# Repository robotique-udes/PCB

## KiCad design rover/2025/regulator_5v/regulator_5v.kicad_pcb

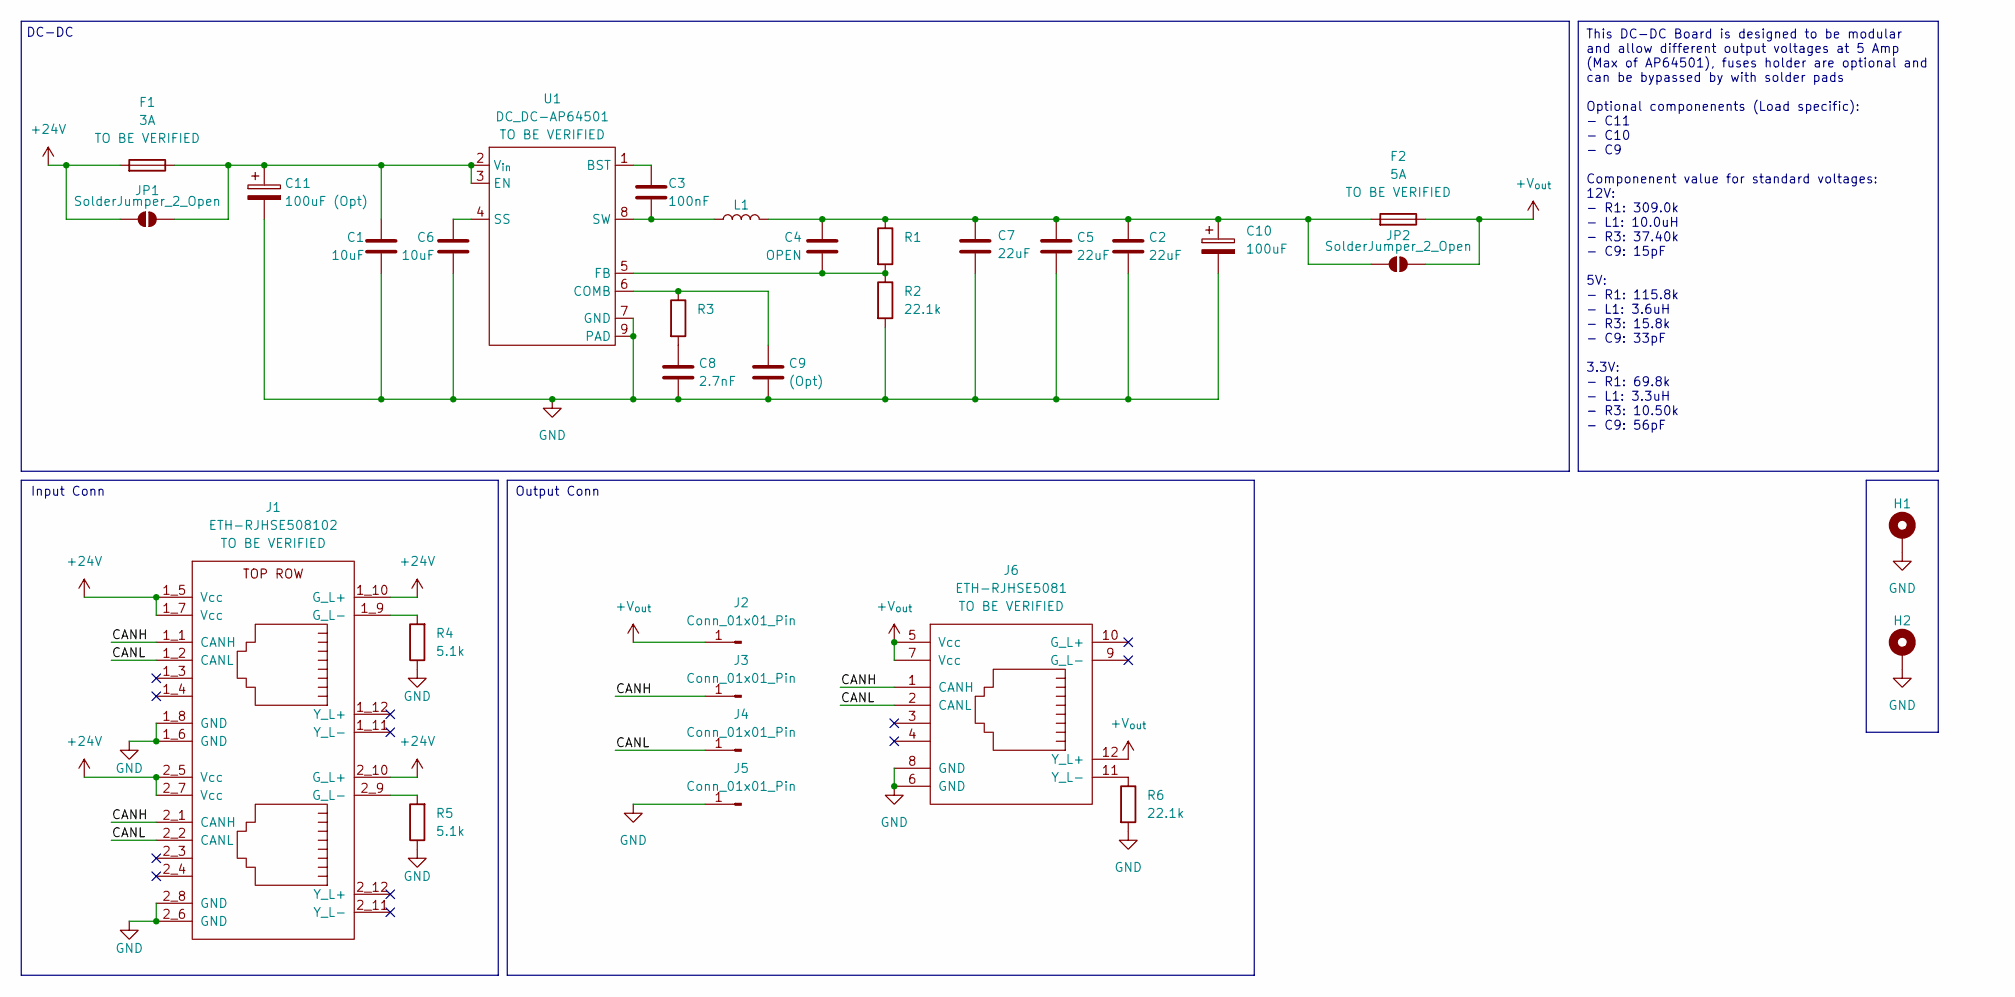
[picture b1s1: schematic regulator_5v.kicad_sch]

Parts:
C1, C6: 10uF; C_0805_2012Metric_Pad1.18x1.45mm_HandSolder
C2, C5, C7: 22uF; C_0805_2012Metric_Pad1.18x1.45mm_HandSolder
C3: 100nF; C_0805_2012Metric_Pad1.18x1.45mm_HandSolder
C4: OPEN; C_0805_2012Metric_Pad1.18x1.45mm_HandSolder
C8: 2.7nF; C_0805_2012Metric_Pad1.18x1.45mm_HandSolder
C9: (Opt); C_0805_2012Metric_Pad1.18x1.45mm_HandSolder
C10: 100uF; CP_Elec_6.3x7.7
C11: 100uF (Opt); CP_Elec_6.3x7.7
F1: 3A; FuseHolder-3588-20
F2: 5A; FuseHolder-3588-20
H1, H2: MountingHole_Pad; MountingHole_3.2mm_M3_DIN965_Pad_TopBottom
J1: ETH-RJHSE508102
J2, J3, J4, J5: Conn_01x01_Pin; Pad_SMD_1x3mm
J6: ETH-RJHSE5081
JP1, JP2: SolderJumper_2_Open; SolderJumper-2_P1.3mm_Open_TrianglePad1.0x1.5mm
L1: L_SXN_SMDRI125
R1, R3: C_0805_2012Metric_Pad1.18x1.45mm_HandSolder
R2, R6: 22.1k; C_0805_2012Metric_Pad1.18x1.45mm_HandSolder
R4, R5: 5.1k; R_0805_2012Metric_Pad1.20x1.40mm_HandSolder
U1: DC_DC-AP64501; SOIC-8-1EP_3.9x4.9mm_P1.27mm_EP2.29x3mm

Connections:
+24V: F1.1, J1.1_5 (Vcc), J1.1_7 (Vcc), J1.1_10 (G_L+), J1.2_5 (Vcc), J1.2_7 (Vcc), J1.2_10 (G_L+), JP1.1 (A)
+V_{out}: F2.2, J2.1, J6.5 (Vcc), J6.7 (Vcc), J6.12 (Y_L+), JP2.2 (B)
/CANH: J1.1_1 (CANH), J1.2_1 (CANH), J3.1, J6.1 (CANH)
/CANL: J1.1_2 (CANL), J1.2_2 (CANL), J4.1, J6.2 (CANL)
GND: C1.1, C2.1, C5.1, C6.1, C7.1, C8.1, C9.1, C10.2, C11.2, H1.1, H2.1, J1.1_6 (GND), J1.1_8 (GND), J1.2_6 (GND), J1.2_8 (GND), J5.1, J6.6 (GND), J6.8 (GND), R2.2, R4.1, R5.1, R6.2, U1.7 (GND), U1.9 (PAD)
unnamed: C8.2, R3.2
unnamed: J1.1_9 (G_L-), R4.2
unnamed: J1.2_9 (G_L-), R5.2
unnamed: J6.11 (Y_L-), R6.1
unnamed: C1.2, C11.1, F1.2, JP1.2 (B), U1.2 (V_{in}), U1.3 (EN)
unnamed: C2.2, C4.2, C5.2, C7.2, C10.1, F2.1, JP2.1 (A), L1.2, R1.1
unnamed: C3.1, L1.1, U1.8 (SW)
unnamed: C9.2, R3.1, U1.6 (COMB)
unnamed: C6.2, U1.4 (SS)
unnamed: C3.2, U1.1 (BST)
unnamed: C4.1, R1.2, R2.1, U1.5 (FB)

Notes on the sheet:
This DC-DC Board is designed to be modular and allow different output voltages at 5 Amp (Max of AP64501), fuses holder are optional and can be bypassed by with solder pads Optional componenents (Load specific): - C11 - C10 - C9 Componenent value for standard voltages: 12V: - R1: 309.0k - L1: 10.0uH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
Input Conn
DC-DC
Output Conn

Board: 2 copper layers, 31 parts (17 on the bottom side), 16 nets, no tracks yet.

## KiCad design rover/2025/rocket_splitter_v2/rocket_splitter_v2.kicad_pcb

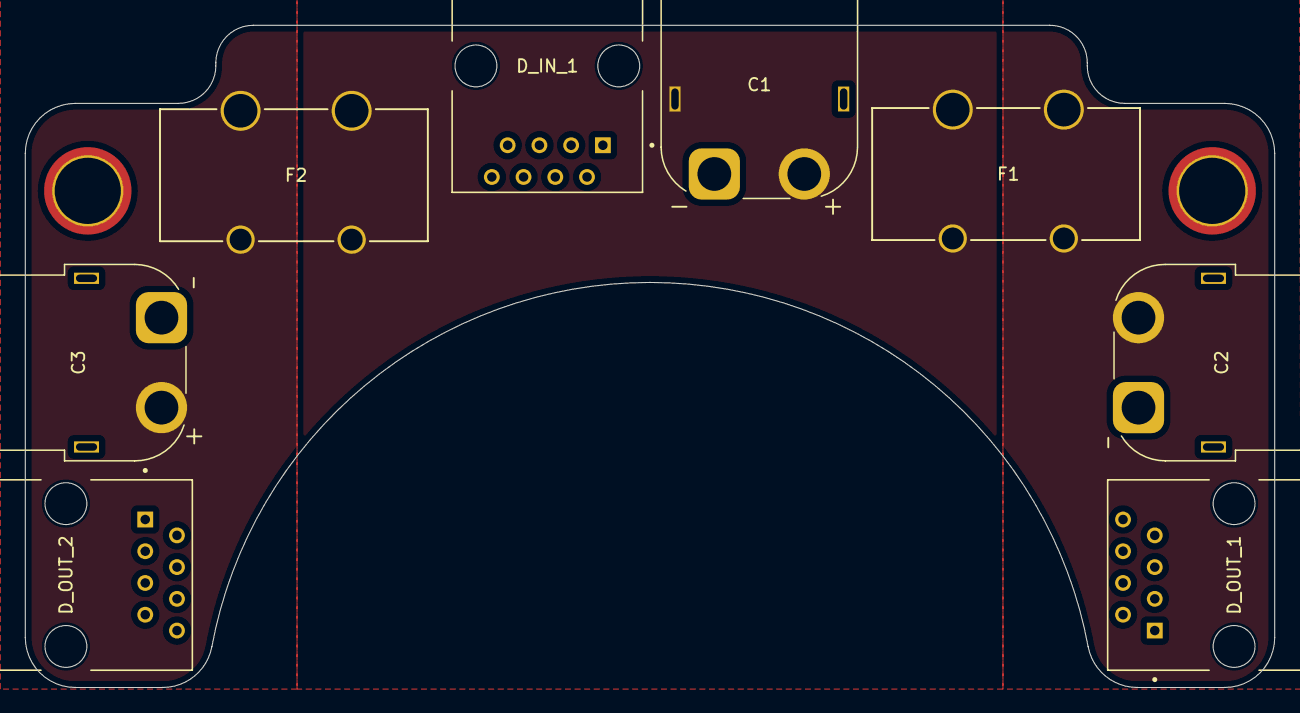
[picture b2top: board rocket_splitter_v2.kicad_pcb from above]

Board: 4 copper layers, 100.0 x 53.0 mm, 10 parts (0 on the bottom side), 7 nets.

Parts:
C1: XT60PW-M; AMASS_XT60PW-M_1x02_P7.20mm_Horizontal
C2, C3: XT60PW-F; AMASS_XT60PW-F_1x02_P7.20mm_Horizontal
D_IN_1: RJ45; AMPHENOL_54601-908WPLF
D_OUT_1, D_OUT_2: RJ45; AMPHENOL_54601-908WPLF
F1, F2: 3550 x2; 3550-2_KEY
H1, H2: MountingHole_Pad; MountingHole_5.3mm_M5_DIN965_Pad_TopBottom

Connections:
+5V: D_IN_1.7, D_OUT_1.7, D_OUT_2.7
+24V: C1.2 (+), F1.1, F1.3, F2.2, F2.4
CANH: D_IN_1.1, D_OUT_1.1, D_OUT_2.1
CANL: D_IN_1.2, D_OUT_1.2, D_OUT_2.2
GND: C1.1 (-), C2.1 (-), C3.1 (-), D_IN_1.8, D_OUT_1.8, D_OUT_2.8, H1.1, H2.1
unnamed: C2.2 (+), F1.2, F1.4
unnamed: C3.2 (+), F2.1, F2.3

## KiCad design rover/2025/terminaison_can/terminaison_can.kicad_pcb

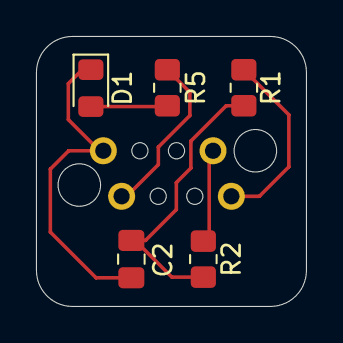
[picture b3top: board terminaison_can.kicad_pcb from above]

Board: 2 copper layers, 15.0 x 15.0 mm, 6 parts (1 on the bottom side), 6 nets.

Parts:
C2: 47nF; C_0805_2012Metric_Pad1.18x1.45mm_HandSolder
CON1: RJ45_MALE-AJP92A8813
D1: LED; LED_0805_2012Metric_Pad1.15x1.40mm_HandSolder
R1, R2: 60; R_0805_2012Metric_Pad1.20x1.40mm_HandSolder
R5: 2k; R_0805_2012Metric_Pad1.20x1.40mm_HandSolder

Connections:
CAN_H: CON1.1, R1.1
CAN_L: CON1.2, R2.2
GND: C2.2, CON1.8, D1.1 (K)
unnamed: C2.1, R1.2, R2.1
unnamed: D1.2 (A), R5.1
VCC: CON1.7, R5.2

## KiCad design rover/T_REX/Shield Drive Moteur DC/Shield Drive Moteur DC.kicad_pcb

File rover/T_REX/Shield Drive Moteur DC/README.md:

# SHIELD Drive Moteur DC
PCB QU'ON SUPPOSE QUI N'EST PAS UTILISÉ SUR LE ROVER

Voici les informations concernant le PCB : Shield Drive Moteur DC 

## Image du PCB en 3D

## Objectifs:
* Contrôler un moteur
* Laisser passer le courant pour connecter d'autres Drive en daisy chain
* Utiliser le protocole CAN bus pour lire et envoyer des informations au Main Board
* Gérer le courant qui passe dans le moteur à l'aide d'une thermistance qui limite le courant
* Sécuriser le moteur à l'aide d'un fusible

## Composants principaux:
* ESP32 DEV KIT V1
* TJA1050 CAN BUS
* Horizontal Amphenol 54602 RJ45
* DELs
* Boutons
* AMASS XT60PW-M Power connectors
* JST 6 pos Horizontal connector
* Thermistor PTC RDT

## Fonctionnement:
* Le ESP32 recoit les commandes par CAN
* Le ESP32 envoit une commande PWM par un connecteur
* La thermistor permet de limiter le courant qui entre dans le circuit à partir du CAN BUS

## PGIO
### Inputs
Name        | GPIO
---         |  ---
BTN1        | D34
BTN2        | D39
BTN3        | D36
INTERRUPT_A | D36
INTERRUPT_A | D36

### Outputs

Name       | GPIO
---        | ---
PWM_Moteur | D26
LED_1      | D32
LED_2      | D33
LED_3      | D25

### Communication

Name    | GPIO
---     | ---
MOSI    | D23
MISO    | D19
SCLK    | D18
CS_1    | D5
CS_2    | D4
SCL     | D22
SDA     | D21
TXD2    | D17
RXD2    | D16

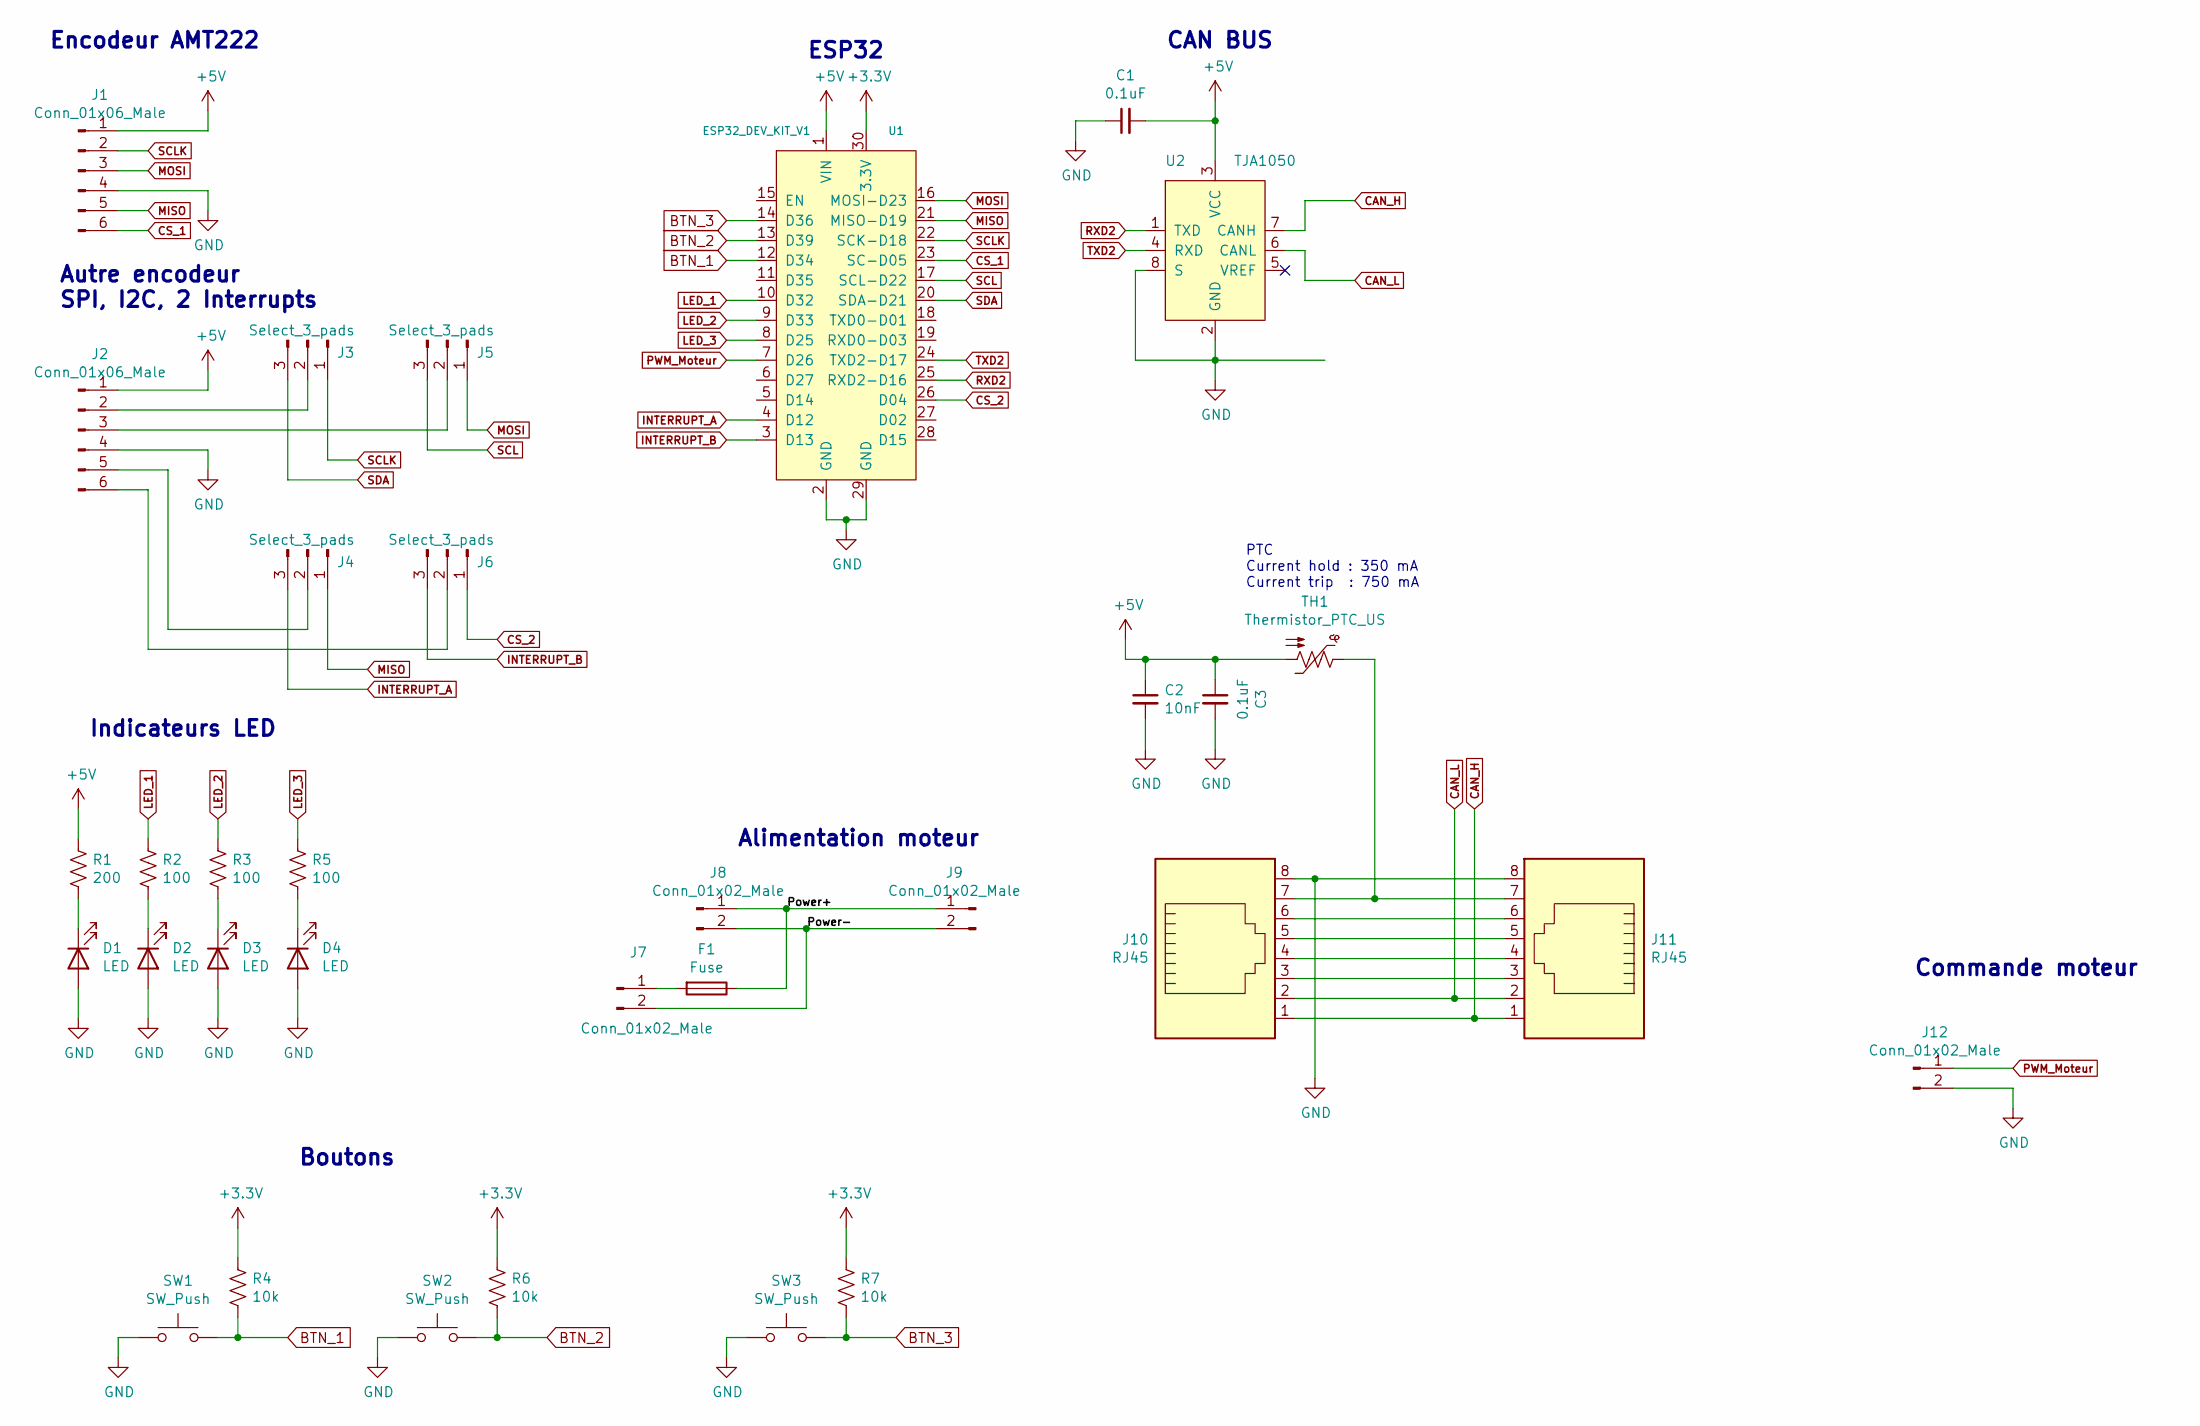
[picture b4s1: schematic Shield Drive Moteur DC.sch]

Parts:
C1, C3: 0.1uF; C_0603_1608Metric_Pad1.08x0.95mm_HandSolder
C2: 10nF; C_0603_1608Metric_Pad1.08x0.95mm_HandSolder
D1: LED; LED_0805_2012Metric_Pad1.15x1.40mm_HandSolder
D2, D3, D4: LED; LED_0805_HandSolder
F1: Fuse; FUSE_3555-2
J1, J2: Conn_01x06_Male; JST-6-Pos-Horizontal
J3, J4, J5, J6: Select_3_pads
J7, J8, J9: Conn_01x02_Male; AMASS_XT60PW-M
J10, J11: RJ45; RJ45_Amphenol_54602-x08_Horizontal
J12: Conn_01x02_Male; JST_EH_B2B-EH-A_1x02_P2.50mm_Vertical
R1: 200; R_0805_2012Metric_Pad1.20x1.40mm_HandSolder
R2, R3, R5: 100; R_0805_2012Metric_Pad1.20x1.40mm_HandSolder
R4, R6, R7: 10k; R_0603_1608Metric_Pad0.98x0.95mm_HandSolder
SW1, SW2, SW3: SW_Push; SW_TS09-63-25-WT-160-SMT-TR
TH1: Thermistor_PTC_US; R_1206_3216Metric_Pad1.30x1.75mm_HandSolder
U1: ESP32_DEV_KIT_V1; MODULE_DEVKIT_V1_ESP32-WROOM-32
U2: TJA1050; SO-8_3.9x4.9mm_P1.27mm

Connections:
+3V3: R4.1, R6.1, R7.1, U1.30 (3.3V)
+5V: C1.2, C2.1, C3.1, J1.1, J2.1, R1.1, TH1.2, U1.1 (VIN), U2.3 (VCC)
/Power+: F1.1, J8.1, J9.1
/Power-: J7.2, J8.2, J9.2
BTN_1: R4.2, SW1.2, U1.12 (D34)
BTN_2: R6.2, SW2.2, U1.13 (D39)
BTN_3: R7.2, SW3.2, U1.14 (D36)
CAN_H: J10.1, J11.1, U2.7 (CANH)
CAN_L: J10.2, J11.2, U2.6 (CANL)
CS_1: J1.6, U1.23 (SC-D05)
CS_2: J6.1, U1.26 (D04)
GND: C1.1, C2.2, C3.2, D1.2 (A), D2.2 (A), D3.2 (A), D4.2 (A), J1.4, J2.4, J10.8, J11.8, J12.2, SW1.1, SW2.1, SW3.1, U1.2 (GND), U1.29 (GND), U2.2 (GND), U2.8 (S)
INTERRUPT_A: J4.3, U1.4 (D12)
INTERRUPT_B: J6.3, U1.3 (D13)
LED_1: R2.1, U1.10 (D32)
LED_2: R3.1, U1.9 (D33)
LED_3: R5.1, U1.8 (D25)
MISO: J1.5, J4.1, U1.21 (MISO-D19)
MOSI: J1.3, J5.1, U1.16 (MOSI-D23)
unnamed: D1.1 (K), R1.2
unnamed: D2.1 (K), R2.2
unnamed: D3.1 (K), R3.2
unnamed: D4.1 (K), R5.2
unnamed: F1.2, J7.1
unnamed: J2.2, J3.2
unnamed: J2.3, J5.2
unnamed: J2.5, J4.2
unnamed: J2.6, J6.2
unnamed: J10.3, J11.3
unnamed: J10.4, J11.4
unnamed: J10.5, J11.5
unnamed: J10.6, J11.6
unnamed: J10.7, J11.7, TH1.1
PWM_Moteur: J12.1, U1.7 (D26)
RXD2: U1.25 (RXD2-D16), U2.1 (TXD)
SCL: J5.3, U1.17 (SCL-D22)
SCLK: J1.2, J3.1, U1.22 (SCK-D18)
SDA: J3.3, U1.20 (SDA-D21)
TXD2: U1.24 (TXD2-D17), U2.4 (RXD)

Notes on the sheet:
CAN BUS
Encodeur AMT222
Indicateurs LED
ESP32
Autre encodeur SPI, I2C, 2 Interrupts
Commande moteur
Alimentation moteur
PTC Current hold : 350 mA Current trip : 750 mA
Boutons

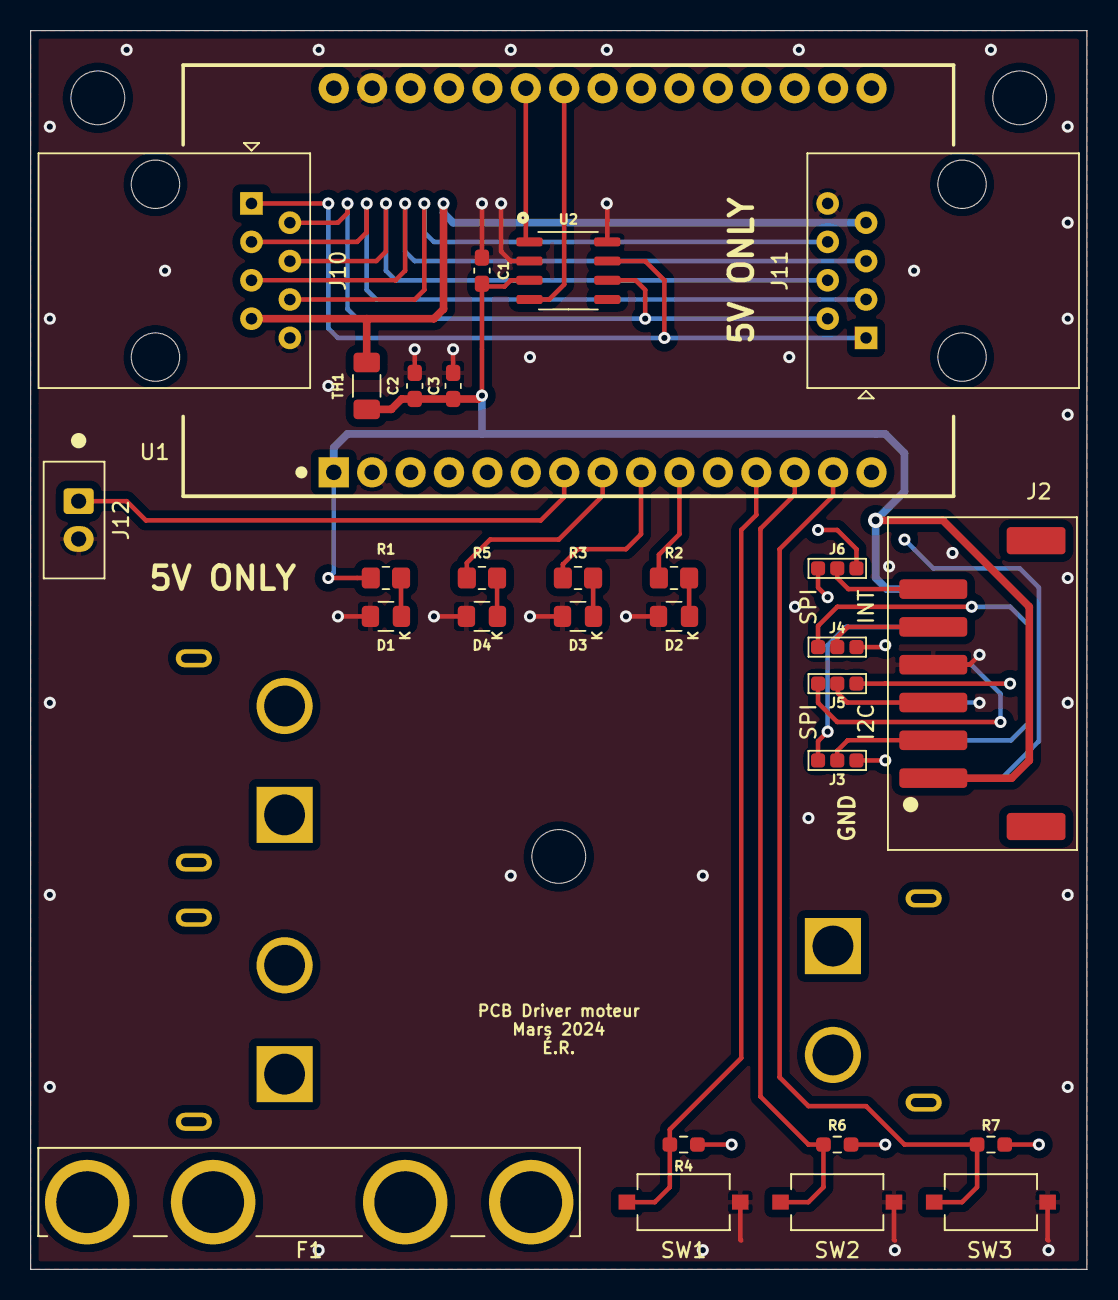
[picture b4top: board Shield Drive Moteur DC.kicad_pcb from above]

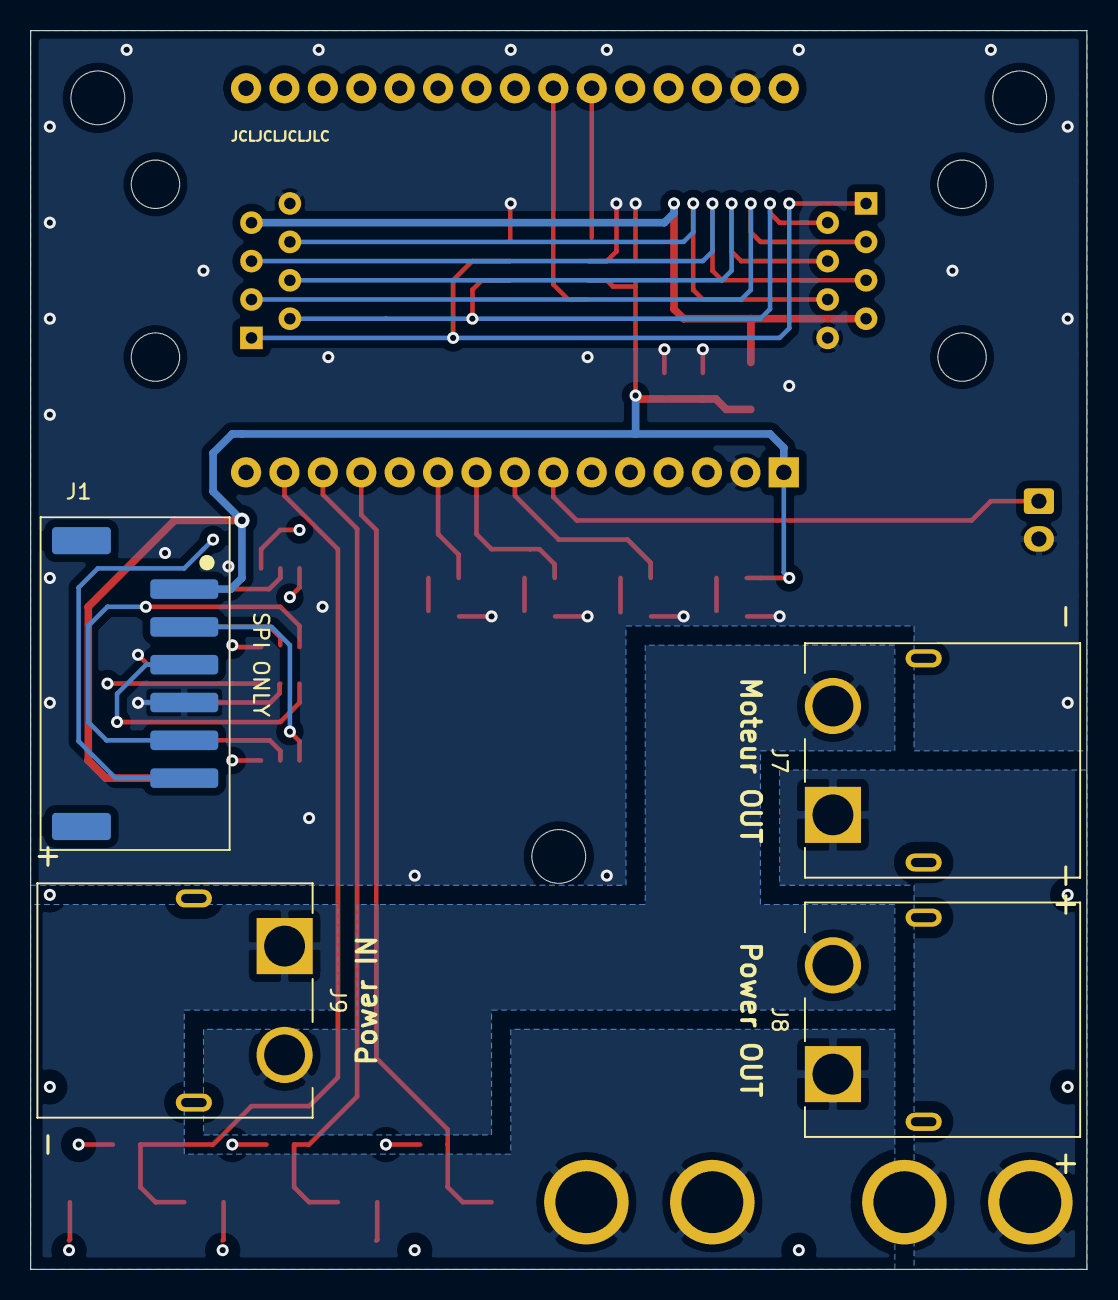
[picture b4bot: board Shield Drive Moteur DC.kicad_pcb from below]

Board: 4 copper layers, 69.8 x 81.9 mm, 33 parts (4 on the bottom side), 39 nets.

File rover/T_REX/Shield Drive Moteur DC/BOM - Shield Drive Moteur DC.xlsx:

PCB Shield Drive Moteur DC |  | 45352
Nbr PCB = | 1
Ref | Nbr | Description | # Digikey | # Manufacturer | Coût/unité ($) | Coût * Nbr
U1 | 1 | Esp32 DEVKIT V1 | - | - |  | 0
U2 | 1 | IC TRANSCEIVER HALF 1/1 8SO | 568-10292-1-ND | TJA1050T/CM,118 | 2.91 | 2.91
J1 - J2 | 2 | CONN HEADER SMD R/A 6POS 2.5MM | 455-2264-1-ND | S6B-XH-SM4-TB | 1.47 | 2.94
J7 - J8 - J9 | 3 | CONN RIGHT ANGLE XT60 MALE | - | XT60PW-M | 1.1599999999999999 | 3.4799999999999995
J10 - J11 | 2 | CONN MOD JACK 8P8C R/A UNSHLD | 609-5081-ND | 54601-908WPLF | 1 | 2
J12 | 1 | CONN HEADER VERT 2POS 2.5MM | 455-B2B-XH-A-ND | B2B-XH-A | 0.22 | 0.22
C1 - C3 | 2 | CAP CER 0.1UF 50V Y5V 0603 | 311-1343-1-ND | CC0603ZRY5V9BB104 | 0.14000000000000001 | 0.28000000000000003
C2 | 1 | CAP CER 10000PF 50V X7R 0603 | 311-1085-1-ND | CC0603KRX7R9BB103 | 0.14000000000000001 | 0.14000000000000001
D1 - D2 - D3 - D4 | 4 | LED GREEN CLEAR 0805 SMD | 732-4986-1-ND | 150080VS75000 | 0.28999999999999998 | 1.1599999999999999
R1 | 1 | RES SMD 200 OHM 1% 1/8W 0805 | YAG3707CT-ND | AC0805FR-07200RL | 0.15 | 0.15
R2 - R3 - R5 | 3 | RES 100 OHM 1% 1/8W 0805 | 311-100CRCT-ND | RC0805FR-07100RL | 0.15 | 0.44999999999999996
R4 - R6 - R7 | 3 | RES 10K OHM 1% 1/10W 0603 | 311-10.0KHRCT-ND | RC0603FR-0710KL | 0.15 | 0.44999999999999996
TH1 | 1 | PTC RESET FUSE 30V 350MA 1206 | 507-1801-1-ND | 0ZCJ0035AF2E | 0.35 | 0.35
F1 | 1 | FUSE BLOCK BLADE 500V 50A PCB | 36-3555-2-ND | 3555-2 | 2.98 | 2.98
SW1 - SW2 - SW3 | 3 | SWITCH TACTILE SPST-NO 0.05A 12V | 2223-TS09-63-25-WT-160-SMT-TRCT-ND | TS09-63-25-WT-160-SMT-TR | 0.37 | 1.1099999999999999
 |  |  |  |  | Coût total | 18.619999999999997

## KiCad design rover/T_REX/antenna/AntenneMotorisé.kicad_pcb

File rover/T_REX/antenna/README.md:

# Antenna
PCB servant à motoriser l'antenne de la Base Station

Voici les informations concernant le PCB : Antenna

## Image du PCB en 3D

## Objectifs:
* Alimenter les antennes de la Base Station
* Changer l'orientation des Antennes par commandes envoyés par Wi-Fi
* alimenter une caméra montée sur l'antenne
* Permettre la connections de tous les périphériques en utilisant seulement un câble Ethernet vers la Base Station (Switch Ethernet)

## Composants principaux:
* ESP32 DEV KIT V1
* 24V-5V DC-DC converter
* A4988 Stepper driver
* Ports Ethernets
* AMS1117-3.3 (LDO)
* TVS diodes

## Fonctionnement:
Le circuit est alimenté en 24V qui est régulée par un AC-DC.
Une tension de 5V est régulée par un Buck converter à partir du 24V.
Une tension de 3V3 est régulée par un LDO utilisé à partir du 5V.
Les prises en bas, sont des prises qui sortent du boitier et qui servent à connecter tous les périphériques.
Les prises en haut permettent aux périphériques de se connecter dans une Switch Ethernet afin de les multiplexer et ainsi d'avoir seulemenet un câble qui doive aller vers la Base Station.
Un Driver de Stepper permet de faire tourner un moteur qui fait tourner l'antenne sur elle-même.
Les antennes ont besoin d'être alimentés à une tension de 24V, donc le circuit sert de POE pour un maximum de 2 antennes.

## PGIO
### Outputs

Name         | GPIO
---          | ---
LED_BUILDIN  | D2
STEPPIN      | D37
DIRPIN       | D38
ENABLEPIN    | D39

### Communication

Name    | GPIO
---     | ---
USBN    | D19
USBP    | D20

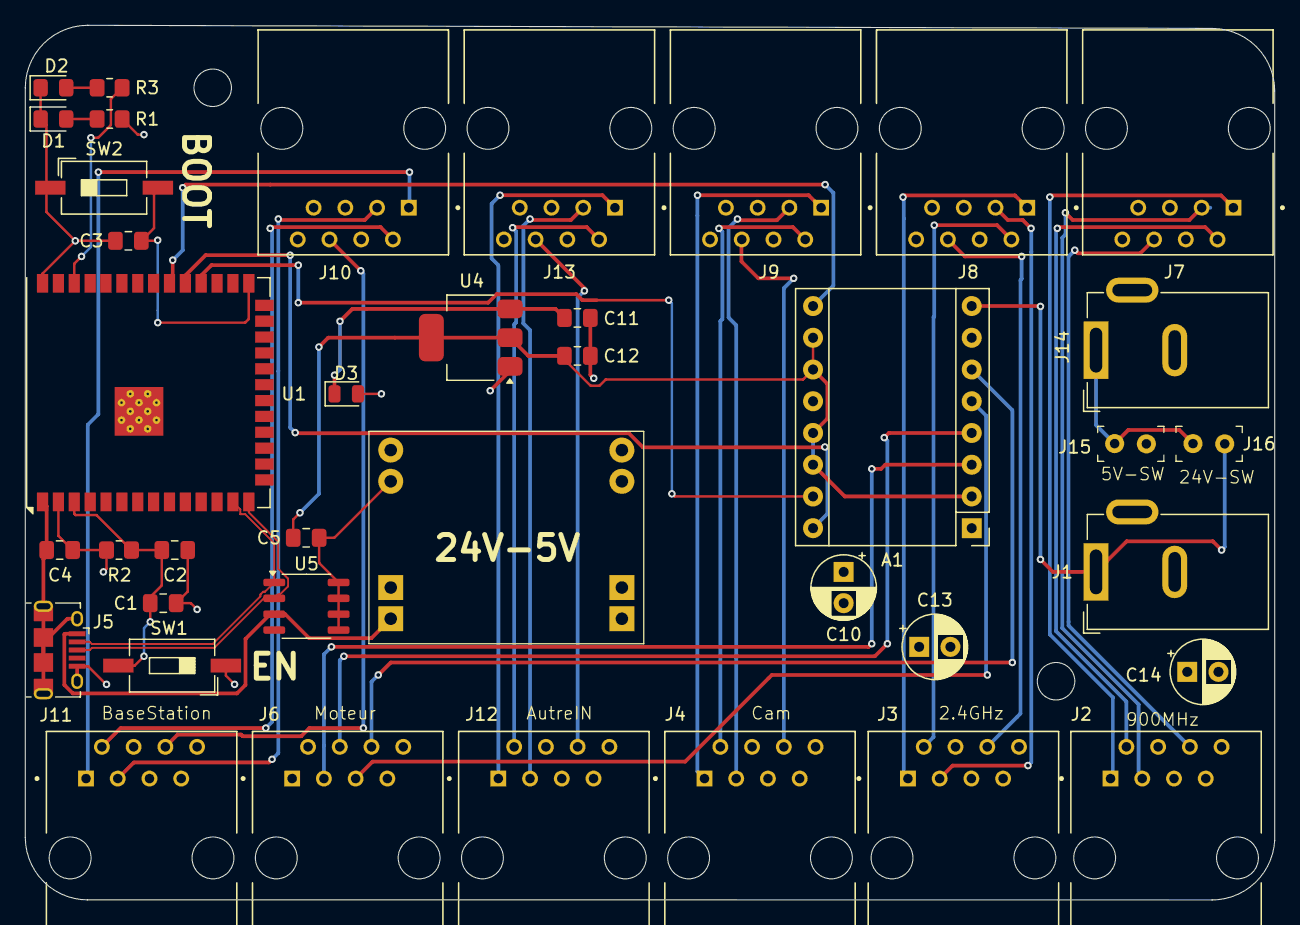
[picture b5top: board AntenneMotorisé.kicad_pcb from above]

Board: 4 copper layers, 100.0 x 70.0 mm, 39 parts (1 on the bottom side), 40 nets.

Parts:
A1: Pololu_Breakout_A4988; Pololu_Breakout-16_15.2x20.3mm
C1, C3, C5: 100nF; C_0805_2012Metric_Pad1.18x1.45mm_HandSolder
C2: 1uF; C_0805_2012Metric_Pad1.18x1.45mm_HandSolder
C4: 22uF; C_0805_2012Metric_Pad1.18x1.45mm_HandSolder
C10, C13, C14: 100uF; CP_Radial_D5.0mm_P2.50mm
C11: 10u; C_0805_2012Metric_Pad1.18x1.45mm_HandSolder
C12: 22u; C_0805_2012Metric_Pad1.18x1.45mm_HandSolder
D1: R; LED_0805_2012Metric_Pad1.15x1.40mm_HandSolder
D2: B; LED_0805_2012Metric_Pad1.15x1.40mm_HandSolder
D3: 1N4004; D_0805_2012Metric
J1, J14: Barrel_Jack; BarrelJack_GCT_DCJ200-10-A_Horizontal
J2: POE900; AMPHENOL_54601-908WPLF
J3: POE2.4; AMPHENOL_54601-908WPLF
J4: CameraIN; AMPHENOL_54601-908WPLF
J5: BaseStation; AMPHENOL_54601-908WPLF
J6: Moteur; AMPHENOL_54601-908WPLF
J7: LAN900; AMPHENOL_54601-908WPLF
J8: LAN2.4; AMPHENOL_54601-908WPLF
J9: LANCamera; AMPHENOL_54601-908WPLF
J10: SwitchOut; AMPHENOL_54601-908WPLF
J11: USB_B_Micro; USB_Micro-B_Amphenol_10118194_Horizontal
J12: Eth4IN; AMPHENOL_54601-908WPLF
J13: LAN4; AMPHENOL_54601-908WPLF
J15, J16: M20-9990246; PinHeader_1x2_P2.54mm
R1, R3: 330; R_0805_2012Metric_Pad1.20x1.40mm_HandSolder
R2: 10K TBV; R_0805_2012Metric_Pad1.20x1.40mm_HandSolder
SW1, SW2: TS09-63-25-WT-160-SMT-TR; SW_DIP_SPSTx01_Slide_6.7x4.1mm_W8.61mm_P2.54mm_LowProfile
U1: ESP32-S3-WROOM-1
U3: MP1584EN-Buck Converter; Buck_7V-24V_5V
U4: AMS1117-3.3; SOT-223-3_TabPin2
U5: SO-8_3.9x4.9mm_P1.27mm

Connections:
+3.3V: A1.2 (VDD), A1.10 (MS1), A1.11 (MS2), A1.13 (~RESET), A1.14 (~SLEEP), C4.1, C5.1, C12.1, R1.1, R2.1, U1.2 (3V3), U4.2 (VO)
+5V: D3.2 (A), J11.1 (VBUS), J15.1, U3.5 (Vout+), U3.6 (Vout+), U5.3
+24V: A1.8 (VMOT), C10.1, C13.1, C14.1, J1.1, J2.4, J2.5, J3.4, J3.5, J16.1, U3.1 (Vin+), U3.2 (Vin+)
DIRPIN: A1.16 (DIR), U1.31 (IO38)
ENABLEPIN: A1.9 (~ENABLE), U1.32 (IO39)
EN_PB: C1.2, C2.1, R2.2, SW1.2, U1.3 (EN)
GND: A1.1 (GND), A1.7 (GND), A1.12 (MS3), C1.1, C2.2, C3.1, C4.2, C5.2, C10.2, C11.2, C12.2, C13.2, C14.2, D1.1 (K), D2.1 (K), J1.2, J2.7, J2.8, J3.7, J3.8, J11.5 (GND), J11.6 (Shield), J14.2, SW1.1, SW2.1, U1.1 (GND), U1.40 (GND), U1.41 (GND), U3.3 (Vin-), U3.4 (Vin-), U3.7 (Vout-), U3.8 (Vout-), U4.1 (GND), U5.5, U5.6, U5.7, U5.8
GPIO_0: C3.2, SW2.2, U1.27 (IO0)
LED_BUILDIN: R3.2, U1.38 (IO2)
unnamed: D1.2 (A), R1.2
unnamed: D2.2 (A), R3.1
unnamed: C11.1, D3.1 (K), U4.3 (VI)
unnamed: J4.1, J9.1
unnamed: J4.2, J9.2
unnamed: J4.3, J9.3
unnamed: J4.6, J9.6
unnamed: J5.1, J10.1
unnamed: J5.2, J10.2
unnamed: J5.3, J10.3
unnamed: J5.6, J10.6
unnamed: J12.1, J13.1
unnamed: J12.2, J13.2
unnamed: J12.3, J13.3
unnamed: J12.6, J13.6
unnamed: J14.1, J15.2, J16.2
OUT1A: A1.3 (1B), J6.3
OUT1B: A1.4 (1A), J6.4
OUT2A: A1.5 (2A), J6.5
OUT2B: A1.6 (2B), J6.6
Rx+_2.4: J3.3, J8.3
Rx+_900: J2.3, J7.3
Rx-_2.4: J3.6, J8.6
Rx-_900: J2.6, J7.6
STEPPIN: A1.15 (STEP), U1.30 (IO37)
Tx+_2.4: J3.1, J8.1
Tx+_900: J2.1, J7.1
Tx-_2.4: J3.2, J8.2
Tx-_900: J2.2, J7.2
USB_N: J11.2 (D-), U1.13 (IO19), U5.1
USB_P: J11.3 (D+), U1.14 (IO20), U5.2
